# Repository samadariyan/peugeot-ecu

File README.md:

# Peugeot ECU

## Peugeot Pars Petrol

Engine Eloctronic Control Unit

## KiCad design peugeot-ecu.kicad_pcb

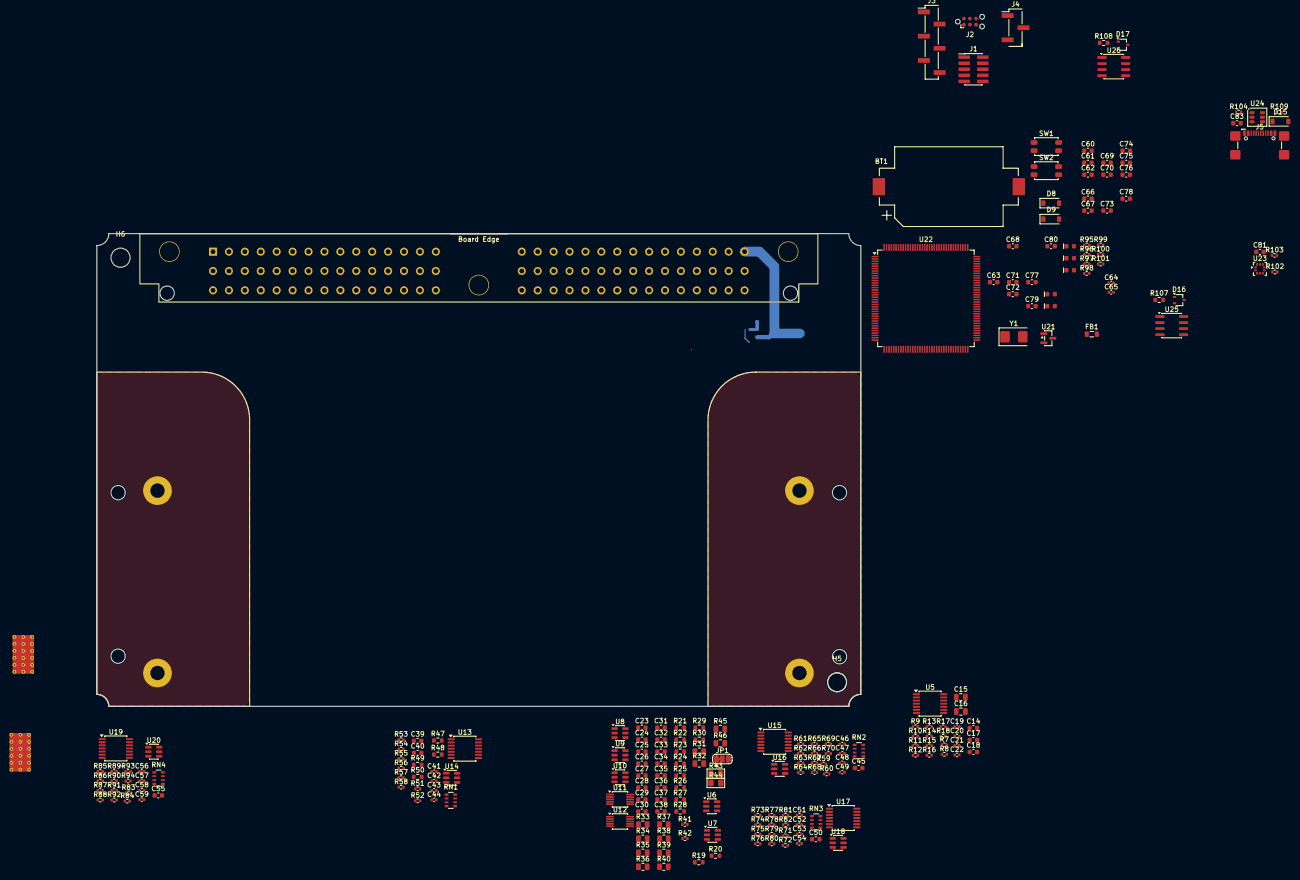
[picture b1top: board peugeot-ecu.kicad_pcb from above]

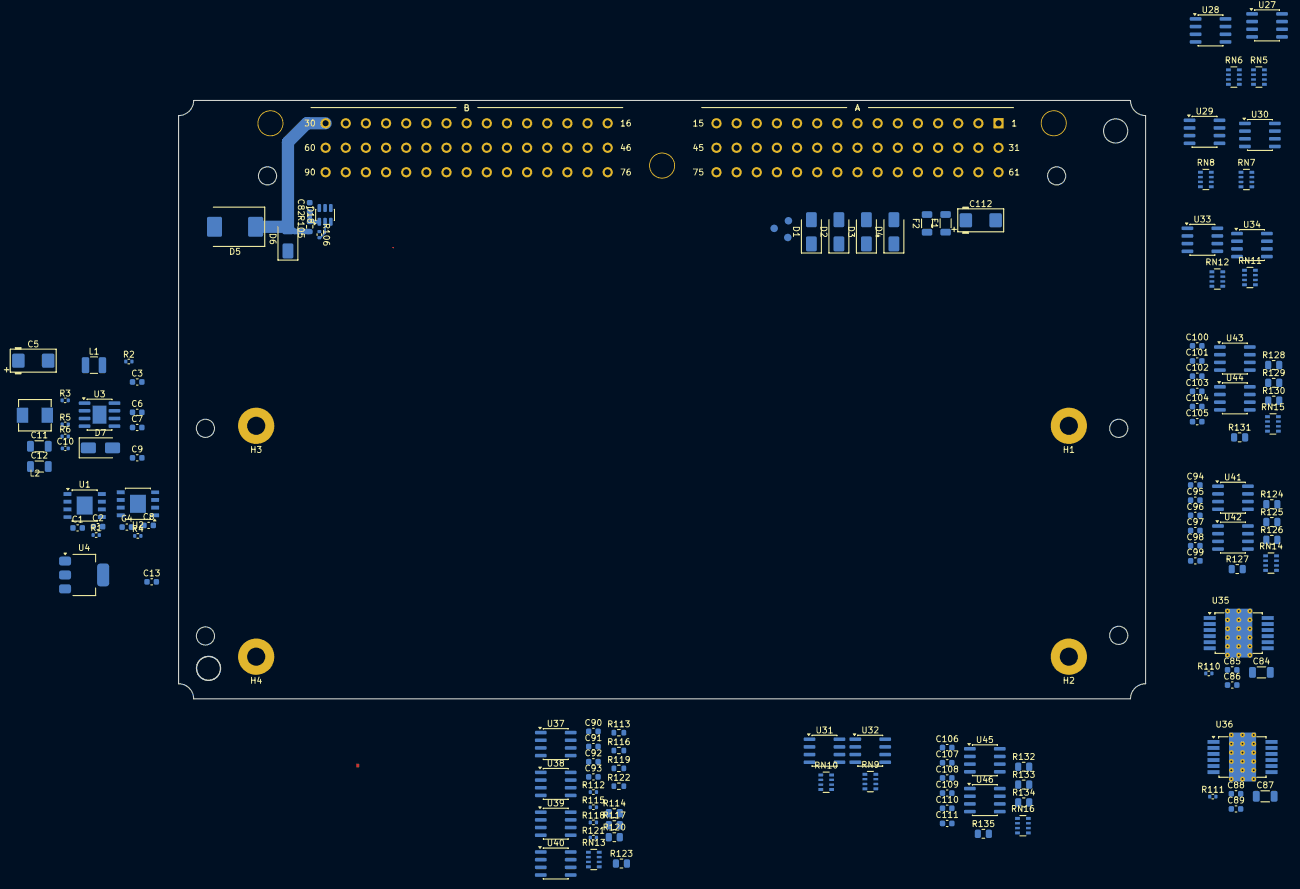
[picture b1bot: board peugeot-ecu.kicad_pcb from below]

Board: 4 copper layers, 357 parts (132 on the bottom side), 287 nets.

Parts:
BT1: Battery_Cell; BatteryHolder_Keystone_1060_1x2032
C1, C2, C4, C6, C8, C37, C82: 1u; C_0603_1608Metric
C3, C13, C66, C67, C75, C77, C78, C80: 4.7u; C_0603_1608Metric
C5, C112: 56u; CP_EIA-6032-28_Kemet-C
C7, C14, C85, C86, C88, C89, C90, C91, C92, C93, C96, C97, C98, C99, C102, C103, C104, C105, C108, C109, C110, C111: 10n; C_0603_1608Metric
C9, C38, C39, C40, C45, C50, C55, C60, C61, C62, C63, C69, C70, C72, C73, C74, C76, C79, C81, C83, C94, C95, C100, C101, C106, C107: 100n; C_0603_1608Metric
C10, C19, C20: 330p; C_0402_1005Metric
C11, C12, C84, C87: 10u; C_1206_3216Metric
C15, C16: 3.3n; C_0805_2012Metric
C17, C18: 680p; C_0603_1608Metric
C21, C22: 47p; C_0402_1005Metric
C23, C24, C25, C26, C27, C28, C29, C30, C31, C32, C33, C34, C35, C36: 1n; C_0603_1608Metric
C41, C42, C43, C44, C46, C47, C48, C49, C51, C52, C53, C54, C56, C57, C58, C59: 100n; C_0402_1005Metric
C64, C65: 33p; C_0402_1005Metric
C68, C71: 2.2u; C_0603_1608Metric
D1, D2, D3, D4, D6, D7: D_Schottky; D_SMA
D5: SM15T33CA; D_SMC
D8, D9, D15: schottky; D_SOD-123
D10, D13: GREEN; LED_0603_1608Metric_Green
D11: RED; LED_0603_1608Metric_Red
D12: BLUE; LED_0603_1608Metric_Blue
D14: ORANGE; LED_0603_1608Metric_Orange
D16, D17: PESD1CAN-UX; SOT-323_SC-70
D18: SRV05-4; SOT-23-6
F1, F2: Polyfuse; R_1206_3216Metric
FB1: Ferrite_Bead; L_0805_2012Metric
H1, H2, H3, H4: MountingHole_Pad; MountingHole_3mm_Pad
H5, H6: MountingHole; MountingHole_4mm
H7, H8, H9, H10: MountingHole; MountingHole_3mm
HS1: Heatsink_Generic_Dual; Heatsink_Dual_70x31mm
J1: Conn_02x05_Odd_Even; PinHeader_2x05_P1.27mm_Vertical_SMD
J2: Conn_01x06; Tag-Connect_TC2030-IDC-NL_2x03_P1.27mm_Vertical
J3: Conn_01x06; PinHeader_1x06_P2.54mm_Vertical_SMD_Pin1Left
J4: Conn_01x03; PinHeader_1x03_P2.54mm_Vertical_SMD_Pin1Left
J5: USB_C_Receptacle_USB2.0_16P; USB_C_Receptacle_GCT_USB4110
J6: Conn_01x90_3Row_Header; 90pin_sealed_header
JP1: Jumper_3_Bridged12; SolderJumper-3_P1.3mm_Bridged12_RoundedPad1.0x1.5mm
L1: 2.2u; L_1210_3225Metric
L2: 10u; MWSA0503
R1, R3, R4, R55, R56, R57, R58, R67, R68, R69, R70, R79, R80, R81, R82, R91, R92, R93, R94, R95, R96, R106, R110, R111, R112, R115, R118, R121: 10k; R_0402_1005Metric
R2: 1; R_0402_1005Metric
R5, R13, R14: 12k; R_0402_1005Metric
R6: 68k; R_0402_1005Metric
R7, R8, R17, R18: 33k; R_0402_1005Metric
R9, R10, R15, R16, R109: 100k; R_0402_1005Metric
R11, R12, R59, R60, R61, R62, R71, R72, R73, R74, R83, R84, R85, R86: 470k; R_0402_1005Metric
R19, R20, R21, R22, R23, R24, R25, R26, R27, R28, R29, R30, R47, R48, R49, R50: 2.7k; R_0603_1608Metric
R31, R32, R33, R34, R35, R36, R37, R38, R45, R46, R114, R117, R120, R123: 4.7k; R_0805_2012Metric
R39, R40: DNP; R_0805_2012Metric
R41, R42, R102, R103: 1k; R_0402_1005Metric
R43, R44: DNP; R_0805_2012Metric_Pad1.15x1.40mm_HandSolder
R51, R52, R53, R54, R63, R64, R65, R66, R75, R76, R77, R78, R87, R88, R89, R90, R104: 5.6k; R_0402_1005Metric
R97, R98, R99, R100, R101: 330; R_0402_1005Metric
R105: 82k; R_0603_1608Metric
R107, R108, R113, R116, R119, R122: 120; R_0603_1608Metric
R124, R125, R126, R127, R128, R129, R130, R131, R132, R133, R134, R135: 100; R_0805_2012Metric
RN1, RN2, RN3, RN4, RN13: 10k; R_Array_Convex_4x0603
RN5, RN6, RN7, RN8, RN9, RN10, RN11, RN12, RN14, RN15, RN16: 1k; R_Array_Convex_4x0603
SW1, SW2: SW_Push; SW_SPST_EVQP2_ShortPushTravel_H2.5mm
TP1, TP2, TP3: 1.25mm; TestPoint-1.25mm
U1, U2: TLS115; Infineon_PG-DSO-8-43
U3: LMR14020; SOIC-8-1EP_3.9x4.9mm_P1.27mm_EP2.29x3mm
U4: AMS1117-3.3; SOT-223-3_TabPin2
U5, U13, U15, U17, U19: MCP6004; TSSOP-14_4.4x5mm_P0.65mm
U6, U7, U10: SN74LVC2G17C; SOT-23-6
U8, U9, U14, U16, U18, U20: SRV05-4; SOT-23-6
U11, U12: MAX9924; MSOP-10_3x3mm_P0.5mm
U21: REF3333; SOT-23
U22: STM32F767ZITx; LQFP-144_20x20mm_P0.5mm
U23: LPS25HB; ST_HLGA-10_2.5x2.5mm_P0.6mm_LayoutBorder3x2y
U24: USBLC6-2SC6; SOT-23-6
U25, U26: TJA1051T-3; SOIC-8_3.9x4.9mm_P1.27mm
U27, U28, U29, U30, U31, U32, U33, U34: VNLD5160; SOIC-8_3.9x4.9mm_P1.27mm
U35, U36: TLE9201SG; Infineon_PG-DSO-12-9_ThermalVias
U37, U38, U39, U40: BTS4175SGA; SOIC-8_3.9x4.9mm_P1.27mm
U41, U42, U43, U44, U45, U46: MIC4427; SOIC-8_3.9x4.9mm_P1.27mm
Y1: 8MHz; Crystal_SMD_5032-2Pin_5.0x3.2mm

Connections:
+3V3: C13.1, C60.2, C61.2, C62.2, C66.2, C67.2, C69.2, C70.2, C73.2, C74.2, C75.2, C76.2, C78.2, C79.1, C80.1, C81.1, D9.2 (A), D10.2 (A), D18.5 (VP), FB1.1, FB1.2, J1.1, J2.1, J3.1, R1.2, R4.2, R7.2, R45.1, R46.1, R95.2, R102.1, R103.1, R110.2, R111.2, R112.2, R115.2, R118.2, R121.2, SW2.2, TP3.1, U4.2 (VO), U5.4 (V+), U22.17 (VDD), U22.30 (VDD), U22.33 (VDDA), U22.39 (VDD), U22.52 (VDD), U22.62 (VDD), U22.72 (VDD), U22.84 (VDD), U22.95 (VDDUSB), U22.108 (VDD), U22.121 (VDDSDMMC), U22.131 (VDD), U22.143 (PDR_ON), U22.144 (VDD), U23.1 (Vdd_IO), U23.6 (~CS), U23.10 (VDD), U25.5 (VIO), U26.5 (VIO), U35.2 (VSO), U36.2 (VSO)
+5V: C10.1, C11.1, C12.1, C38.1, C39.1, C45.1, C50.1, C55.1, C94.2, C95.2, C100.2, C101.2, C106.2, C107.2, D15.1 (K), JP1.1 (A), L2.2, R6.2, R41.1, TP2.1, U1.5 (ADJ), U2.5 (ADJ), U4.3 (VI), U6.5 (VCC), U7.5 (VCC), U8.5 (VP), U9.5 (VP), U10.5 (VCC), U11.9 (INT_THRS), U11.10 (VCC), U12.10 (VCC), U13.4 (V+), U14.5 (VP), U15.4 (V+), U16.5 (VP), U17.4 (V+), U18.5 (VP), U19.4 (V+), U20.5 (VP), U21.1 (IN), U25.3 (VCC), U26.3 (VCC), U41.6 (V_{S}), U42.6 (V_{S}), U43.6 (V_{S}), U44.6 (V_{S}), U45.6 (V_{S}), U46.6 (V_{S})
/5V_SENSOR_1: C2.1, C40.2, J6.10 (A10), J6.40 (A40), R19.1, R20.1, R21.1, R22.1, R27.1, R28.1, R47.1, R48.1, R49.1, R50.1, U1.1 (OUT)
/5V_SENSOR_2: C8.1, J6.14 (A14), J6.47 (B47), U2.1 (OUT)
/12V_MR: C84.2, C87.2, C112.1, D1.1 (K), D2.1 (K), D3.1 (K), D4.1 (K), J6.29 (B29), U35.4 (VS), U36.4 (VS), U37.5 (VS), U37.6 (VS), U37.7 (VS), U37.8 (VS), U38.5 (VS), U38.6 (VS), U38.7 (VS), U38.8 (VS), U39.5 (VS), U39.6 (VS), U39.7 (VS), U39.8 (VS), U40.5 (VS), U40.6 (VS), U40.7 (VS), U40.8 (VS)
/12V_RAW: D5.1 (A1), D6.2 (A), J6.30 (B30), R105.1
/12v_PROT: C1.1, C4.1, D6.1 (K), F1.1, F2.1, L1.1, R2.1, U1.7 (EN), U1.8 (IN), U2.7 (EN), U2.8 (IN)
/AT1: J6.39 (A39), R47.2, RN1.1 (R1.1)
/AT2: J6.46 (B46), R48.2, RN1.2 (R2.1)
/AT3: J6.35 (A35), R49.2, RN1.3 (R3.1)
/AT4: J6.36 (A36), R50.2, RN1.4 (R4.1)
/AV1: J6.11 (A11), R59.1, RN2.1 (R1.1)
/AV2: J6.37 (A37), R60.1, RN2.2 (R2.1)
/AV3: J6.15 (A15), R61.1, RN2.3 (R3.1)
/AV4: J6.68 (A68), R62.1, RN2.4 (R4.1)
/AV5: J6.70 (A70), R71.1, RN3.1 (R1.1)
/AV6: J6.17 (B17), R72.1, RN3.2 (R2.1)
/AV8: J6.65 (A65), R74.1, RN3.4 (R4.1)
/AV9: J6.66 (A66), R83.1, RN4.1 (R1.1)
/AV10: J6.67 (A67), R84.1, RN4.2 (R2.1)
/AV11: J6.22 (B22), R85.1, RN4.3 (R3.1)
/CAN2+: D17.2 (A2), J6.77 (B77), R108.1, U26.7 (CANH)
/CAN2-: D17.1 (A1), J6.76 (B76), R108.2, U26.6 (CANL)
/CAN+: D16.2 (A2), J6.53 (B53), R107.1, U25.7 (CANH)
/CAN-: D16.1 (A1), J6.64 (A64), R107.2, U25.6 (CANL)
/DIGITAL_1: C23.1, J6.41 (A41), R19.2, R23.2
/DIGITAL_2: C31.1, J6.63 (A63), R27.2, R29.2
/DIGITAL_3: C32.1, J6.86 (B86), R28.2, R30.2
/DIGITAL_4: C25.1, J6.71 (A71), R21.2, R25.2
/DIGITAL_5: C24.1, R20.2, R24.2
/DIGITAL_6: C26.1, J6.5 (A5), R22.2, R26.2
/ETB1+: C85.2, J6.3 (A3), U35.5 (OUT1)
/ETB1-: C86.1, J6.2 (A2), U35.7 (OUT2)
/ETB2+: C88.2, J6.32 (A32), U36.5 (OUT1)
/ETB2-: C89.1, J6.62 (A62), U36.7 (OUT2)
/HS1: C90.1, J6.59 (B59), R114.1, U37.3 (OUT)
/HS2: C91.1, J6.60 (B60), R117.1, U38.3 (OUT)
/HS3: C92.1, J6.89 (B89), R120.1, U39.3 (OUT)
/HS4: C93.1, J6.90 (B90), R123.1, U40.3 (OUT)
/IGN1: C96.1, J6.61 (A61), R124.1
/IGN2: C97.1, J6.31 (A31), R125.1
/IGN3: C98.1, J6.48 (B48), R126.1
/IGN4: C99.1, J6.52 (B52), R127.1
/IGN5: C102.1, J6.56 (B56), R128.1
/IGN6: C103.1, J6.78 (B78), R129.1
/IGN7: C104.1, J6.79 (B79), R130.1
/IGN8: C105.1, J6.49 (B49), R131.1
/IGN9: C108.1, J6.54 (B54), R132.1
/IGN10: C109.1, J6.55 (B55), R133.1
/IGN11: C110.1, J6.84 (B84), R134.1
/IGN12: C111.1, J6.19 (B19), R135.1
/KNOCK_1: C15.2, J6.45 (A45)
/KNOCK_2: C16.2, J6.8 (A8)
/LS1: J6.42 (A42), U27.8 (D1)
/LS2: J6.20 (B20), U27.6 (D2)
/LS3: J6.23 (B23), U28.8 (D1)
/LS4: J6.24 (B24), U28.6 (D2)
/LS5: J6.25 (B25), U29.8 (D1)
/LS6: J6.26 (B26), U29.6 (D2)
/LS7: J6.27 (B27), U30.8 (D1)
/LS8: J6.50 (B50), U30.6 (D2)
/LS9: J6.57 (B57), U31.8 (D1)
/LS10: J6.58 (B58), U31.6 (D2)
/LS11: J6.80 (B80), U32.8 (D1)
/LS12: J6.82 (B82), U32.6 (D2)
/LS13: D3.2 (A), J6.87 (B87), U33.8 (D1)
/LS14: D1.2 (A), J6.88 (B88), U33.6 (D2)
/LS16: D2.2 (A), J6.81 (B81), U34.6 (D2)
/VR1+: J6.72 (A72), R31.2
/VR1-: J6.73 (A73), R32.2
/VR2+: J6.6 (A6), R33.2
/VR2-: J6.7 (A7), R34.2
/etb-1/DIR: U22.79 (PD10), U35.1 (DIR)
/etb-1/DIS: R110.1, U22.80 (PD11), U35.11 (DIS)
/etb-1/PWM: U22.81 (PD12), U35.12 (PWM)
/etb-2/DIR: U22.78 (PD9), U36.1 (DIR)
/etb-2/DIS: R111.1, U22.77 (PD8), U36.11 (DIS)
/etb-2/PWM: U22.82 (PD13), U36.12 (PWM)
/highside_quad/IN1: RN13.4 (R4.1), U22.101 (PA9)
/highside_quad/IN2: RN13.3 (R3.1), U22.100 (PA8)
/highside_quad/IN3: RN13.2 (R2.1), U22.86 (PD15)
/highside_quad/IN4: RN13.1 (R1.1), U22.85 (PD14)
/ign1/IN1: RN14.8 (R1.2), U22.118 (PD4), U41.2 (INA)
/ign1/IN2: RN14.7 (R2.2), U22.117 (PD3), U41.4 (INB)
/ign1/IN3: RN14.6 (R3.2), U22.99 (PC9), U42.2 (INA)
/ign1/IN4: RN14.5 (R4.2), U22.98 (PC8), U42.4 (INB)
/ign2/IN1: RN15.8 (R1.2), U22.97 (PC7), U43.2 (INA)
/ign2/IN2: RN15.7 (R2.2), U22.93 (PG8), U43.4 (INB)
/ign2/IN3: RN15.6 (R3.2), U22.92 (PG7), U44.2 (INA)
/ign2/IN4: RN15.5 (R4.2), U22.91 (PG6), U44.4 (INB)
/ign3/IN1: RN16.8 (R1.2), U22.90 (PG5), U45.2 (INA)
/ign3/IN2: RN16.7 (R2.2), U22.89 (PG4), U45.4 (INB)
/ign3/IN3: RN16.6 (R3.2), U22.88 (PG3), U46.2 (INA)
/ign3/IN4: RN16.5 (R4.2), U22.87 (PG2), U46.4 (INB)
/knock/FILTERED_1: C19.2, U5.6 (-), U5.7, U22.14 (PF4)
/knock/FILTERED_2: C20.2, U5.8, U5.9 (-), U22.15 (PF5)
/knock/V_mid: C14.2, R7.1, R8.1, U5.3 (+), U5.12 (+)
/lowside_quad1/IN1: RN5.8 (R1.2), RN6.4 (R4.1), U22.123 (PD7)
/lowside_quad1/IN2: RN5.7 (R2.2), RN6.3 (R3.1), U22.124 (PG9)
/lowside_quad1/IN3: RN5.6 (R3.2), RN6.2 (R2.1), U22.125 (PG10)
/lowside_quad1/IN4: RN5.5 (R4.2), RN6.1 (R1.1), U22.126 (PG11)
/lowside_quad2/IN1: RN7.8 (R1.2), RN8.4 (R4.1), U22.127 (PG12)
/lowside_quad2/IN2: RN7.7 (R2.2), RN8.3 (R3.1), U22.128 (PG13)
/lowside_quad2/IN3: RN7.6 (R3.2), RN8.2 (R2.1), U22.129 (PG14)
/lowside_quad2/IN4: RN7.5 (R4.2), RN8.1 (R1.1), U22.134 (PB4)
/lowside_quad3/IN1: RN9.8 (R1.2), RN10.4 (R4.1), U22.135 (PB5)
/lowside_quad3/IN2: RN9.7 (R2.2), RN10.3 (R3.1), U22.136 (PB6)
/lowside_quad3/IN3: RN9.6 (R3.2), RN10.2 (R2.1), U22.137 (PB7)
/lowside_quad3/IN4: RN9.5 (R4.2), RN10.1 (R1.1), U22.139 (PB8)
/lowside_quad4/IN1: RN11.8 (R1.2), RN12.4 (R4.1), U22.140 (PB9)
/lowside_quad4/IN2: RN11.7 (R2.2), RN12.3 (R3.1), U22.141 (PE0)
/lowside_quad4/IN3: RN11.6 (R3.2), RN12.2 (R2.1), U22.142 (PE1)
/lowside_quad4/IN4: RN11.5 (R4.2), RN12.1 (R1.1), U22.1 (PE2)
/mcu/5V_SENSOR_1_PG: R1.1, U1.4 (PG), U22.9 (PC15)
/mcu/5V_SENSOR_2_PG: R4.1, U2.4 (PG), U22.8 (PC14)
/mcu/12V_DIVIDED: C82.1, D18.1 (IO1), R105.2, R106.1, U22.43 (PA7)
/mcu/AT1: R51.1, R55.2, U22.44 (PC4)
/mcu/AT2: R52.1, R56.2, U22.45 (PC5)
/mcu/AT3: R53.1, R57.2, U22.46 (PB0)
/mcu/AT4: R54.1, R58.2, U22.47 (PB1)
/mcu/AUX_SPI_CS: J3.2, U22.18 (PF6)
/mcu/AUX_SPI_MISO: J3.4, U22.20 (PF8)
/mcu/AUX_SPI_MOSI: J3.5, U22.21 (PF9)
/mcu/AUX_SPI_SCK: J3.3, U22.19 (PF7)
/mcu/AV1: R63.1, R67.2, U22.26 (PC0)
/mcu/AV2: R64.1, R68.2, U22.27 (PC1)
/mcu/AV3: R65.1, R69.2, U22.28 (PC2)
/mcu/AV4: R66.1, R70.2, U22.29 (PC3)
/mcu/AV5: R75.1, R79.2, U22.34 (PA0)
/mcu/AV6: R76.1, R80.2, U22.35 (PA1)
/mcu/AV7: R77.1, R81.2, U22.36 (PA2)
/mcu/AV8: R78.1, R82.2, U22.37 (PA3)
/mcu/AV9: R87.1, R91.2, U22.40 (PA4)
/mcu/AV10: R88.1, R92.2, U22.41 (PA5)
/mcu/AV11: R89.1, R93.2, U22.42 (PA6)
/mcu/BARO_SCL: R103.2, U22.69 (PB10), U23.2 (SCL)
/mcu/BARO_SDA: R102.2, U22.70 (PB11), U23.4 (SDA)
/mcu/BOOT0: R96.1, SW2.1, U22.138 (BOOT0)
/mcu/CAN2_RX: U22.73 (PB12), U26.4 (RXD)
/mcu/CAN2_TX: U22.74 (PB13), U26.1 (TXD)
/mcu/CAN_RX: U22.114 (PD0), U25.4 (RXD)
/mcu/CAN_TX: U22.115 (PD1), U25.1 (TXD)
/mcu/DIGITAL1: U6.6, U22.96 (PC6)
/mcu/DIGITAL2: U10.6, U22.64 (PE11)
/mcu/DIGITAL3: U10.4, U22.65 (PE12)
/mcu/DIGITAL4: U7.6, U22.67 (PE14)
/mcu/DIGITAL5: U6.4, U22.66 (PE13)
/mcu/DIGITAL6: U7.4, U22.68 (PE15)
/mcu/LED1: D11.2 (A), U22.2 (PE3)
/mcu/LED2: D12.2 (A), U22.3 (PE4)
/mcu/LED3: D13.2 (A), U22.4 (PE5)
/mcu/LED4: D14.2 (A), U22.5 (PE6)
/mcu/SWCLK: J1.4, J2.4, U22.109 (PA14)
/mcu/SWDIO: J1.2, J2.2, U22.105 (PA13)
/mcu/UART_RX: J4.2, U22.122 (PD6)
/mcu/UART_TX: J4.1, U22.119 (PD5)
/mcu/USB_D+: J5.A6 (D+), U22.104 (PA12), U24.1 (L1), U24.6 (L1)
/mcu/USB_D-: J5.A7 (D-), U22.103 (PA11), U24.3 (L2), U24.4 (L2)
/mcu/VR_1: R44.1, R45.2, U11.7 (COUT), U22.58 (PE7)
/mcu/VR_2: R46.2, U12.7 (COUT), U22.59 (PE8)
/mcu/nRESET: C72.2, J1.10, J2.3, R95.1, SW1.2, U22.25 (NRST)
/psu/12v_PROT_C: C5.1, C6.1, L1.2, U3.2 (VIN), U3.3 (EN)
/quad_analog3/IN4: R86.1, RN4.4 (R4.1)
/quad_analog3/OUT4: R90.1, R94.2
GND: BT1.2 (-), C1.2, C2.2, C3.2, C4.2, C5.2, C6.2, C7.2, C8.2, C11.2, C12.2, C13.2, C14.1, C17.1, C18.1, C21.1, C22.1, C23.2, C24.2, C25.2, C26.2, C27.2, C28.2, C29.2, C30.2, C31.2, C32.2, C33.2, C34.2, C37.2, C38.2, C39.2, C40.1, C41.2, C42.2, C43.2, C44.2, C45.2, C46.2, C47.2, C48.2, C49.2, C50.2, C51.2, C52.2, C53.2, C54.2, C55.2, C56.2, C57.2, C58.2, C59.2, C60.1, C61.1, C62.1, C63.2, C64.2, C65.2, C66.1, C67.1, C68.2, C69.1, C70.1, C71.2, C72.1, C73.1, C74.1, C75.1, C76.1, C77.2, C78.1, C79.2, C80.2, C81.2, C82.2, C83.2, C84.1, C85.1, C86.2, C87.1, C88.1, C89.2, C90.2, C91.2, C92.2, C93.2, C94.1, C95.1, C96.2, C97.2, C98.2, C99.2, C100.1, C101.1, C102.2, C103.2, C104.2, C105.2, C106.1, C107.1, C108.2, C109.2, C110.2, C111.2, C112.2, D4.2 (A), D5.2 (A2), D7.2 (A), D16.3 (common), D17.3 (common), D18.2 (VN), H1.1, H2.1, H3.1, H4.1, J1.3, J1.5, J1.9, J2.5, J3.6, J4.3, J5.A1 (GND), J5.A12 (GND), J5.B1 (GND), J5.B12 (GND), J6.1 (A1), J6.9 (A9), J6.12 (A12), J6.13 (A13), J6.16 (B16), J6.21 (B21), J6.28 (B28), J6.33 (A33), J6.34 (A34), J6.38 (A38), J6.43 (A43), J6.44 (A44), J6.51 (B51), J6.69 (A69), J6.74 (A74), J6.75 (A75), J6.83 (B83), JP1.3 (B), R3.2, R5.2, R8.2, R42.1, R55.1, R56.1, R57.1, R58.1, R59.2, R60.2, R61.2, R62.2, R67.1, R68.1, R69.1, R70.1, R71.2, R72.2, R73.1, R73.2, R74.2, R79.1, R80.1, R81.1, R82.1, R83.2, R84.2, R85.2, R86.2, R91.1, R92.1, R93.1, R94.1, R96.2, R97.1, R98.1, R99.1, R100.1, R101.1, R106.2, R109.2, R113.2, R114.2, R116.2, R117.2, R119.2, R120.2, R122.2, R123.2, RN3.3 (R3.1), RN5.1 (R1.1), RN5.2 (R2.1), RN5.3 (R3.1), RN5.4 (R4.1), RN7.1 (R1.1), RN7.2 (R2.1), RN7.3 (R3.1), RN7.4 (R4.1), RN9.1 (R1.1), RN9.2 (R2.1), RN9.3 (R3.1), RN9.4 (R4.1), RN11.1 (R1.1), RN11.2 (R2.1), RN11.3 (R3.1), RN11.4 (R4.1), RN14.1 (R1.1), RN14.2 (R2.1), RN14.3 (R3.1), RN14.4 (R4.1), RN15.1 (R1.1), RN15.2 (R2.1), RN15.3 (R3.1), RN15.4 (R4.1), RN16.1 (R1.1), RN16.2 (R2.1), RN16.3 (R3.1), RN16.4 (R4.1), SW1.1, TP1.1, U1.3 (GND), U1.9 (GND), U2.3 (GND), U2.9 (GND), U3.7 (GND), U3.9 (GND), U4.1 (GND), U5.11 (V-), U6.2 (GND), U7.2 (GND), U8.2 (VN), U9.2 (VN), U10.2 (GND), U11.5 (GND), U12.4 (BIAS), U12.5 (GND), U12.6 (ZERO_EN), U12.9 (INT_THRS), U13.11 (V-), U14.2 (VN), U15.11 (V-), U16.2 (VN), U17.11 (V-), U18.2 (VN), U19.11 (V-), U20.2 (VN), U21.3 (GND), U22.16 (VSS), U22.31 (VSSA), U22.38 (VSS), U22.48 (PB2), U22.51 (VSS), U22.61 (VSS), U22.83 (VSS), U22.94 (VSS), U22.107 (VSS), U22.120 (VSS), U22.130 (VSS), U23.3 (GND), U23.5 (SA0), U23.8 (GND), U23.9 (GND), U24.2 (VN), U25.2 (GND), U25.8 (S), U26.2 (GND), U26.8 (S), U27.5 (S2), U27.7 (S1), U28.5 (S2), U28.7 (S1), U29.5 (S2), U29.7 (S1), U30.5 (S2), U30.7 (S1), U31.5 (S2), U31.7 (S1), U32.5 (S2), U32.7 (S1), U33.5 (S2), U33.7 (S1), U34.5 (S2), U34.7 (S1), U34.8 (D1), U35.6 (GND), U35.13 (GND), U36.6 (GND), U36.13 (GND), U41.3 (GND), U42.3 (GND), U43.3 (GND), U44.3 (GND), U45.3 (GND), U46.3 (GND)
unnamed: BT1.1 (+), D8.2 (A)
unnamed: C3.1, R2.2
unnamed: C15.1, R9.2
unnamed: C16.1, R10.2
unnamed: C17.2, R13.1, R15.2
unnamed: C18.2, R14.1, R16.2
unnamed: C19.1, R15.1, R17.2
unnamed: C20.1, R16.1, R18.2
unnamed: C9.2, D7.1 (K), L2.1, U3.8 (SW)
unnamed: C77.1, D8.1 (K), D9.1 (K), U22.6 (VBAT)
unnamed: D10.1 (K), R97.2
unnamed: D11.1 (K), R98.2
unnamed: D12.1 (K), R99.2
unnamed: D13.1 (K), R100.2
unnamed: D14.1 (K), R101.2
unnamed: D15.2 (A), J5.A4 (VBUS), J5.A9 (VBUS), J5.B4 (VBUS), J5.B9 (VBUS), R104.2, U24.5 (VP)
unnamed: J5.A5 (CC1), R104.1
unnamed: C83.1, J5.S1 (SHIELD), R109.1
unnamed: JP1.2 (C), U11.6 (ZERO_EN)
unnamed: R11.1, R13.2, U5.1
unnamed: R12.1, R14.2, U5.14
unnamed: R31.1, R35.2
unnamed: R32.1, R36.2
unnamed: R33.1, R37.2
unnamed: R34.1, R38.2
unnamed: C41.1, RN1.8 (R1.2), U13.3 (+), U14.6 (IO4)
unnamed: C42.1, RN1.7 (R2.2), U13.5 (+), U14.1 (IO1)
unnamed: C43.1, RN1.6 (R3.2), U13.10 (+), U14.3 (IO2)
unnamed: C44.1, RN1.5 (R4.2), U13.12 (+), U14.4 (IO3)
unnamed: C46.1, RN2.8 (R1.2), U15.3 (+), U16.6 (IO4)
unnamed: C47.1, RN2.7 (R2.2), U15.5 (+), U16.1 (IO1)
unnamed: C48.1, RN2.6 (R3.2), U15.10 (+), U16.3 (IO2)
unnamed: C49.1, RN2.5 (R4.2), U15.12 (+), U16.4 (IO3)
unnamed: C51.1, RN3.8 (R1.2), U17.3 (+), U18.6 (IO4)
unnamed: C52.1, RN3.7 (R2.2), U17.5 (+), U18.1 (IO1)
unnamed: C53.1, RN3.6 (R3.2), U17.10 (+), U18.3 (IO2)
unnamed: C54.1, RN3.5 (R4.2), U17.12 (+), U18.4 (IO3)
unnamed: C56.1, RN4.8 (R1.2), U19.3 (+), U20.6 (IO4)
unnamed: C57.1, RN4.7 (R2.2), U19.5 (+), U20.1 (IO1)
unnamed: C58.1, RN4.6 (R3.2), U19.10 (+), U20.3 (IO2)
unnamed: C59.1, RN4.5 (R4.2), U19.12 (+), U20.4 (IO3)
unnamed: RN6.8 (R1.2), U28.3 (IN2)
unnamed: RN6.7 (R2.2), U28.1 (IN1)
unnamed: RN6.6 (R3.2), U27.3 (IN2)
unnamed: RN6.5 (R4.2), U27.1 (IN1)
unnamed: RN8.8 (R1.2), U30.3 (IN2)
unnamed: RN8.7 (R2.2), U30.1 (IN1)
unnamed: RN8.6 (R3.2), U29.3 (IN2)
unnamed: RN8.5 (R4.2), U29.1 (IN1)
unnamed: RN10.8 (R1.2), U32.3 (IN2)
unnamed: RN10.7 (R2.2), U32.1 (IN1)
unnamed: RN10.6 (R3.2), U31.3 (IN2)
unnamed: RN10.5 (R4.2), U31.1 (IN1)
unnamed: RN12.8 (R1.2), U34.3 (IN2)
unnamed: RN12.7 (R2.2), U34.1 (IN1)
unnamed: RN12.6 (R3.2), U33.3 (IN2)
unnamed: RN12.5 (R4.2), U33.1 (IN1)
unnamed: RN13.8 (R1.2), U40.2 (IN)
unnamed: RN13.7 (R2.2), U39.2 (IN)
unnamed: RN13.6 (R3.2), U38.2 (IN)
unnamed: RN13.5 (R4.2), U37.2 (IN)
unnamed: C9.1, U3.1 (BOOT)
unnamed: C10.2, R5.1, R6.1, U3.5 (FB)
unnamed: R3.1, U3.4 (RT)
unnamed: C7.1, U3.6 (SS)
unnamed: R9.1, R11.2, U5.2 (-)
unnamed: C21.2, R17.1, U5.5 (+)
unnamed: C22.2, R18.1, U5.10 (+)
unnamed: R10.1, R12.2, U5.13 (-)
unnamed: C28.1, R24.1, U6.3, U8.1 (IO1)
unnamed: C27.1, R23.1, U6.1, U8.3 (IO2)
unnamed: C33.1, R29.1, U8.4 (IO3), U10.1
unnamed: C34.1, R30.1, U8.6 (IO4), U10.3
unnamed: C29.1, R25.1, U7.1, U9.1 (IO1), U9.6 (IO4)
unnamed: C30.1, R26.1, U7.3, U9.3 (IO2), U9.4 (IO3)
unnamed: C37.1, R41.2, R42.2, R43.2, U11.4 (BIAS)
unnamed: R43.1, R44.2, U11.8 (EXT)
unnamed: C35.2, R36.1, R39.1, U11.1 (IN+)
unnamed: C35.1, R35.1, R39.2, U11.2 (IN-)
unnamed: C36.2, R38.1, R40.1, U12.1 (IN+)
unnamed: C36.1, R37.1, R40.2, U12.2 (IN-)
unnamed: R51.2, U13.1, U13.2 (-)
unnamed: R52.2, U13.6 (-), U13.7
unnamed: R53.2, U13.8, U13.9 (-)
unnamed: R54.2, U13.13 (-), U13.14
unnamed: R63.2, U15.1, U15.2 (-)
unnamed: R64.2, U15.6 (-), U15.7
unnamed: R65.2, U15.8, U15.9 (-)
unnamed: R66.2, U15.13 (-), U15.14
unnamed: R75.2, U17.1, U17.2 (-)
unnamed: R76.2, U17.6 (-), U17.7
unnamed: R77.2, U17.8, U17.9 (-)
unnamed: R78.2, U17.13 (-), U17.14
unnamed: R87.2, U19.1, U19.2 (-)
unnamed: R88.2, U19.6 (-), U19.7
unnamed: R89.2, U19.8, U19.9 (-)
unnamed: R90.2, U19.13 (-), U19.14
unnamed: C63.1, U21.2 (OUT), U22.32 (VREF+)
unnamed: C64.1, U22.23 (PH0), Y1.1
unnamed: C65.1, U22.24 (PH1), Y1.2
unnamed: C68.1, U22.71 (VCAP_1)
unnamed: C71.1, U22.106 (VCAP_2)
unnamed: R113.1, U37.1 (GND)
unnamed: R112.1, U37.4 (ST)
unnamed: R116.1, U38.1 (GND)
unnamed: R115.1, U38.4 (ST)
unnamed: R119.1, U39.1 (GND)
unnamed: R118.1, U39.4 (ST)
unnamed: R122.1, U40.1 (GND)
unnamed: R121.1, U40.4 (ST)
unnamed: R124.2, U41.7 (OUTA)
unnamed: R125.2, U41.5 (OUTB)
unnamed: R126.2, U42.7 (OUTA)
unnamed: R127.2, U42.5 (OUTB)
unnamed: R128.2, U43.7 (OUTA)
unnamed: R129.2, U43.5 (OUTB)
unnamed: R130.2, U44.7 (OUTA)
unnamed: R131.2, U44.5 (OUTB)
unnamed: R132.2, U45.7 (OUTA)
unnamed: R133.2, U45.5 (OUTB)
unnamed: R134.2, U46.7 (OUTA)
unnamed: R135.2, U46.5 (OUTB)

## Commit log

2026-01-31 initial copy from proteus and external loops
2026-02-03 external loops
2026-02-03 external loops arrangments
2026-02-03 external loops arrangments1
2026-02-03 external loops arrangments2
2026-02-03 cleanup project
2026-02-04 communications updated
2026-02-05 air conditioner updated
